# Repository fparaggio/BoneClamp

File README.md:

-------------------------------------------------------------------------

This file is part of the BoneClamp Data Conversion and Processing System
Copyright (C) 2013 BoneClamp

-------------------------------------------------------------------------

# BoneClamp
BoneClamp is an effort to create a fully programable, real-time, low-cost, data conversion and processing system for the 
[BeagleBone] (http://beagleboard.org/bone).

# More information
[BoneClamp Wiki] (https://potterlab.gatech.edu/main/newman/wiki/index.php?title=BoneClamp)

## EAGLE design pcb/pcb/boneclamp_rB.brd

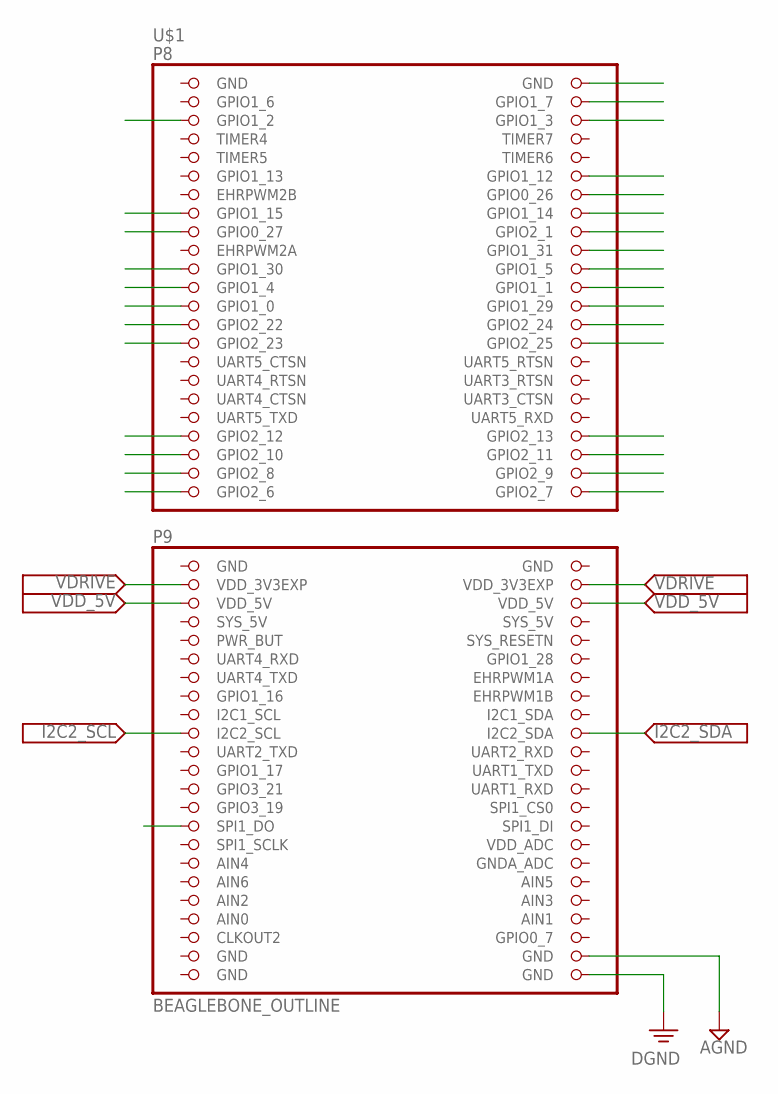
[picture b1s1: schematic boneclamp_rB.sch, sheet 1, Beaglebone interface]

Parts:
U$1: BEAGLEBONE_OUTLINE; BEAGLEBONE_SHIELD

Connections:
AGND: U$1.1 (GND), U$1.47 (GND), U$1.48 (GND), U$1.89 (GND), U$1.90 (GND), U$1.91 (GND); also elsewhere on the board
AIN0: U$1.85 (AIN0)
DGND: U$1.92 (GND); also elsewhere on the board
I2C2_SCL: U$1.65 (I2C2_SCL); also elsewhere on the board
I2C2_SDA: U$1.66 (I2C2_SDA); also elsewhere on the board
SYS_5V: U$1.53 (SYS_5V)
VDD_5V: U$1.51 (VDD_5V), U$1.52 (VDD_5V); also elsewhere on the board
VDRIVE: U$1.49 (VDD_3V3EXP), U$1.50 (VDD_3V3EXP); also elsewhere on the board

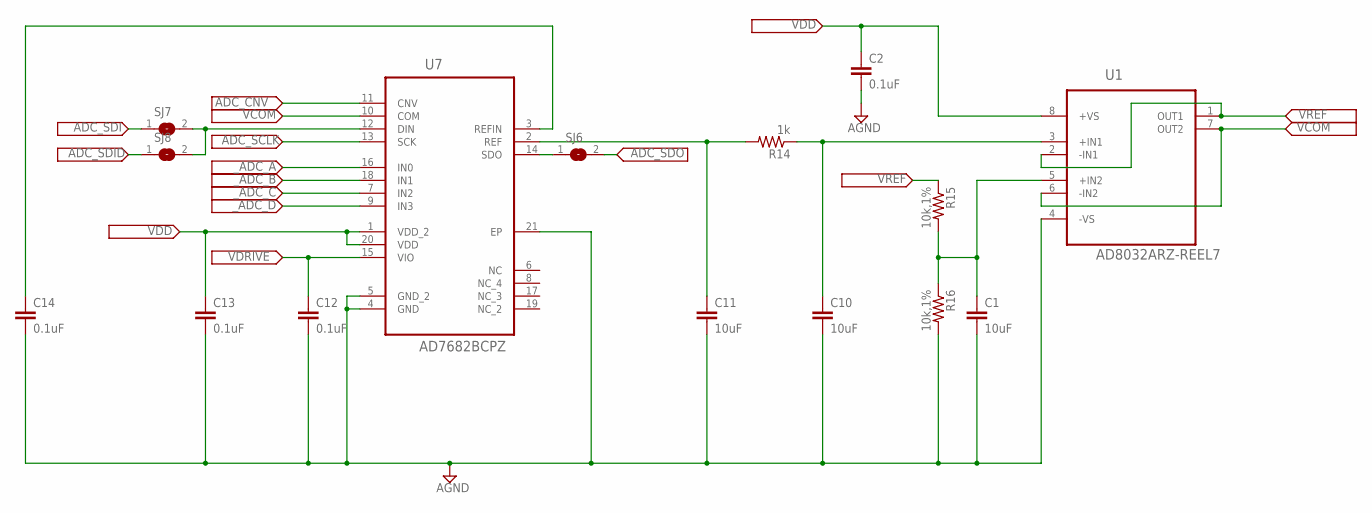
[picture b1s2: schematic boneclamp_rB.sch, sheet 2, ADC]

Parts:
C1, C10, C11: 10uF; C0805
C2, C12, C13, C14: 0.1uF; C0805
R14: 1k; R0805
R15, R16: 10k,1%; R0805
SJ6, SJ7, SJ8: SJ
U1: AD8032ARZ-REEL7; SOIC127P600X175-8N
U7: AD7682BCPZ; QFN50P400X400X100-21N

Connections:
ADC_CNV: U7.11 (CNV)
ADC_SCLK: U7.13 (SCK)
ADC_SDI: SJ7.1
ADC_SDID: SJ8.1
ADC_SDO: SJ6.2
AGND: C1.2, C2.2, C10.2, C11.2, C12.2, C13.2, C14.2, R16.2, U1.4 (-VS), U7.4 (GND), U7.5 (GND_2), U7.21 (EP); also elsewhere on the board
unnamed: C1.1, R15.2, R16.1, U1.5 (+IN2)
unnamed: SJ7.2, SJ8.2, U7.12 (DIN)
unnamed: C11.1, R14.2, U7.2 (REF)
unnamed: C10.1, R14.1, U1.3 (+IN1)
unnamed: C14.1, U7.3 (REFIN)
VCOM: U1.6 (-IN2), U1.7 (OUT2), U7.10 (COM)
VDD: C2.1, C13.1, U1.8 (+VS), U7.1 (VDD_2), U7.20 (VDD); also elsewhere on the board
VDRIVE: C12.1, U7.15 (VIO); also elsewhere on the board
VREF: R15.1, U1.1 (OUT1), U1.2 (-IN1); also elsewhere on the board
_ADC_A: U7.16 (IN0); also elsewhere on the board
_ADC_B: U7.18 (IN1); also elsewhere on the board
_ADC_C: U7.7 (IN2); also elsewhere on the board
_ADC_D: U7.9 (IN3); also elsewhere on the board

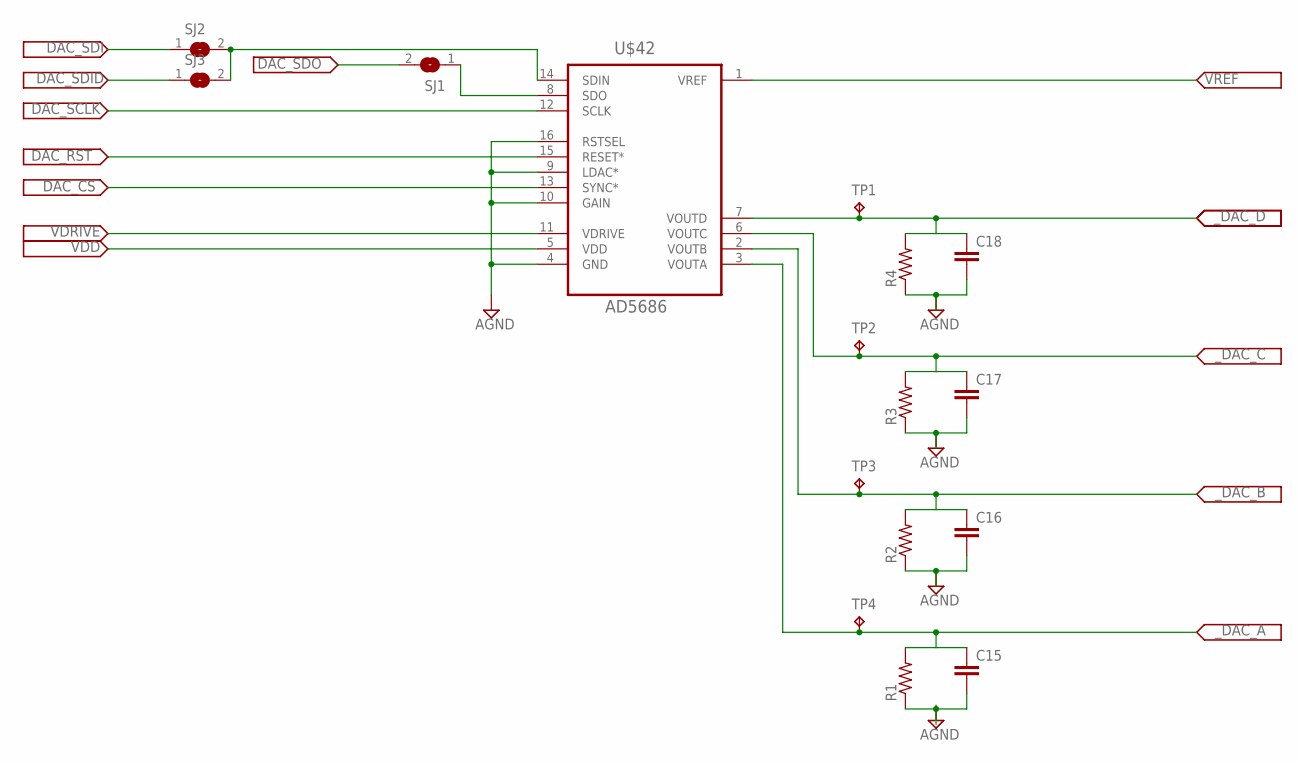
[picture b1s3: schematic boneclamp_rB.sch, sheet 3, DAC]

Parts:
C15, C16, C17, C18: C-EUC0805; C0805
R1, R2, R3, R4: R-US_R0805; R0805
SJ1, SJ2, SJ3: SJ
TP1, TP2, TP3, TP4: TPB1,27; B1,27
U$42: AD5686; MO-153-AB

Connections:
AGND: C16.2, C17.2, C18.2, R2.1, R3.1, R4.1, U$42.4 (GND), U$42.9 (LDAC*), U$42.10 (GAIN), U$42.16 (RSTSEL); also elsewhere on the board
DAC_CS: U$42.13 (SYNC*)
DAC_RST: U$42.15 (RESET*)
DAC_SCLK: U$42.12 (SCLK)
DAC_SDI: SJ2.1
DAC_SDID: SJ3.1
DAC_SDO: SJ1.2
unnamed: SJ1.1, U$42.8 (SDO)
unnamed: SJ2.2, SJ3.2, U$42.14 (SDIN)
unnamed: C15.2, R1.1
VDD: U$42.5 (VDD); also elsewhere on the board
VDRIVE: U$42.11 (VDRIVE); also elsewhere on the board
VREF: U$42.1 (VREF); also elsewhere on the board
_DAC_A: C15.1, R1.2, TP4.TP, U$42.3 (VOUTA); also elsewhere on the board
_DAC_B: C16.1, R2.2, TP3.TP, U$42.2 (VOUTB); also elsewhere on the board
_DAC_C: C17.1, R3.2, TP2.TP, U$42.6 (VOUTC); also elsewhere on the board
_DAC_D: C18.1, R4.2, TP1.TP, U$42.7 (VOUTD); also elsewhere on the board

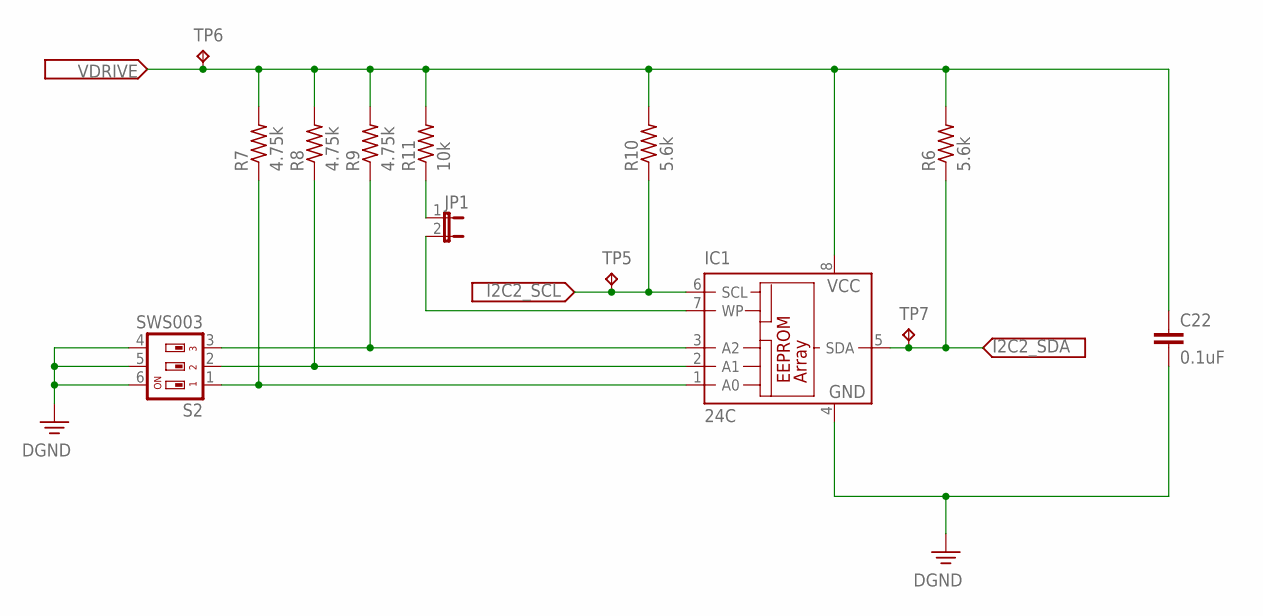
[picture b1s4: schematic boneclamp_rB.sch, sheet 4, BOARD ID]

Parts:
C22: 0.1uF; C0603
IC1: 24C; SO-08
JP1: JP1E; JP1
R6, R10: 5.6k; R0603
R7, R8, R9: 4.75k; R0603
R11: 10k; R0603
S2: SWS003; SMS-003
TP5, TP6, TP7: TPB1,27; B1,27

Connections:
DGND: C22.2, IC1.4 (GND), S2.4, S2.5, S2.6; also elsewhere on the board
I2C2_SCL: IC1.6 (SCL), R10.1, TP5.TP; also elsewhere on the board
I2C2_SDA: IC1.5 (SDA), R6.1, TP7.TP; also elsewhere on the board
unnamed: IC1.1 (A0), R7.1, S2.1
unnamed: IC1.2 (A1), R8.1, S2.2
unnamed: IC1.3 (A2), R9.1, S2.3
unnamed: IC1.7 (WP), JP1.2
unnamed: JP1.1, R11.1
VDRIVE: C22.1, IC1.8 (VCC), R6.2, R7.2, R8.2, R9.2, R10.2, R11.2, TP6.TP; also elsewhere on the board

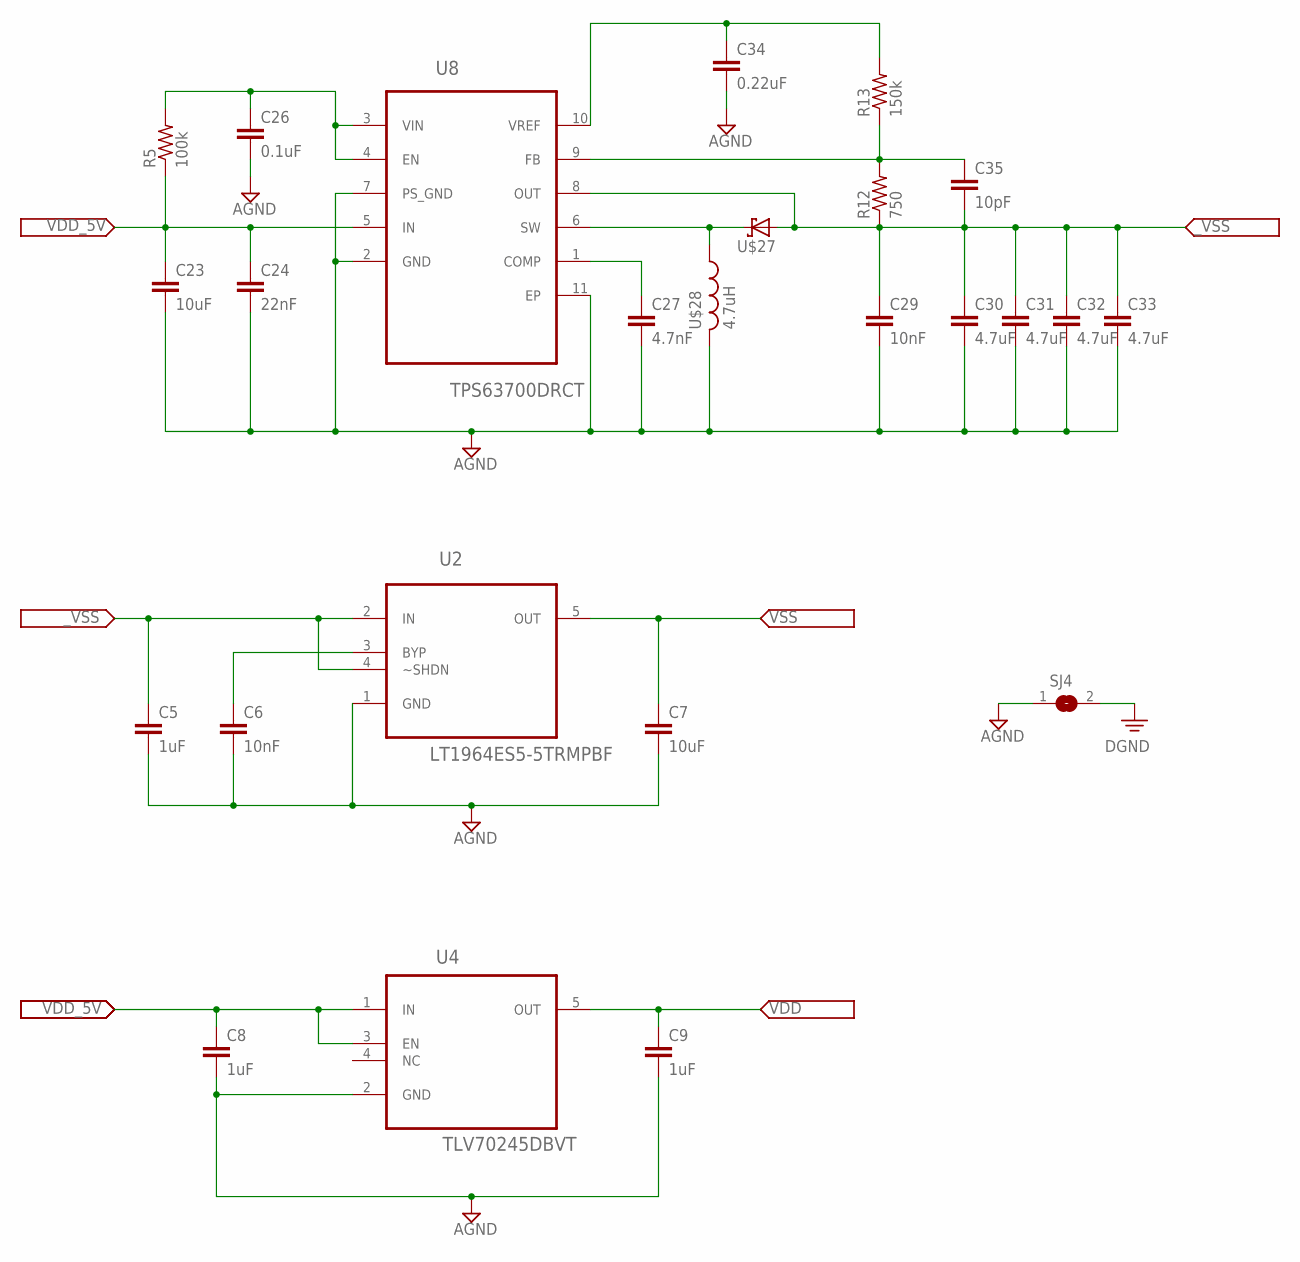
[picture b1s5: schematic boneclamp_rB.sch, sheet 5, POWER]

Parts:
C5, C8, C9: 1uF; C0805
C6, C29: 10nF; C0805
C7, C23: 10uF; C0805
C24: 22nF; C0805
C26: 0.1uF; C0805
C27: 4.7nF; C0805
C30, C31, C32, C33: 4.7uF; C0805
C34: 0.22uF; C0805
C35: 10pF; C0805
R5: 100k; R0805
R12: 750; R0805
R13: 150k; R0805
SJ4: SJ
U2: LT1964ES5-5TRMPBF; SOT95P280X100-5N
U4: TLV70245DBVT; SOT95P280X110-5N
U8: TPS63700DRCT; SON50P300X300X100-11N
U$27: SCHOTTKY-DIODE-2; DO-219AB
U$28: 4.7uH; L4012M

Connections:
AGND: C5.2, C6.2, C7.2, C8.2, C9.2, C23.2, C24.2, C26.2, C27.2, C29.2, C30.2, C31.2, C32.2, C33.2, C34.2, SJ4.1, U2.1 (GND), U4.2 (GND), U8.2 (GND), U8.7 (PS_GND), U8.11 (EP), U$28.2; also elsewhere on the board
DGND: SJ4.2; also elsewhere on the board
unnamed: C6.1, U2.3 (BYP)
unnamed: C26.1, R5.2, U8.3 (VIN), U8.4 (EN)
unnamed: C27.1, U8.1 (COMP)
unnamed: U8.6 (SW), U$27.P$1 (A), U$28.1
unnamed: C35.1, R12.2, R13.1, U8.9 (FB)
unnamed: C34.1, R13.2, U8.10 (VREF)
VDD: C9.1, U4.5 (OUT); also elsewhere on the board
VDD_5V: C8.1, C23.1, C24.1, R5.1, U4.1 (IN), U4.3 (EN), U8.5 (IN); also elsewhere on the board
VSS: C7.1, U2.5 (OUT); also elsewhere on the board
_VSS: C5.1, C29.1, C30.1, C31.1, C32.1, C33.1, C35.2, R12.1, U2.2 (IN), U2.4 (~SHDN), U8.8 (OUT), U$27.P$2 (C)

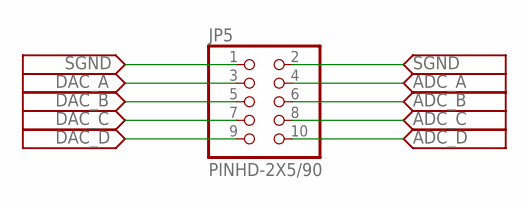
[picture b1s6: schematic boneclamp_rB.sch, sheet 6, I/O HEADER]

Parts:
JP5: PINHD-2X5/90; 2X05/90

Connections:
ADC_A: JP5.4; also elsewhere on the board
ADC_B: JP5.6; also elsewhere on the board
ADC_C: JP5.8; also elsewhere on the board
ADC_D: JP5.10; also elsewhere on the board
DAC_A: JP5.3
DAC_B: JP5.5
DAC_C: JP5.7
DAC_D: JP5.9
SGND: JP5.1, JP5.2

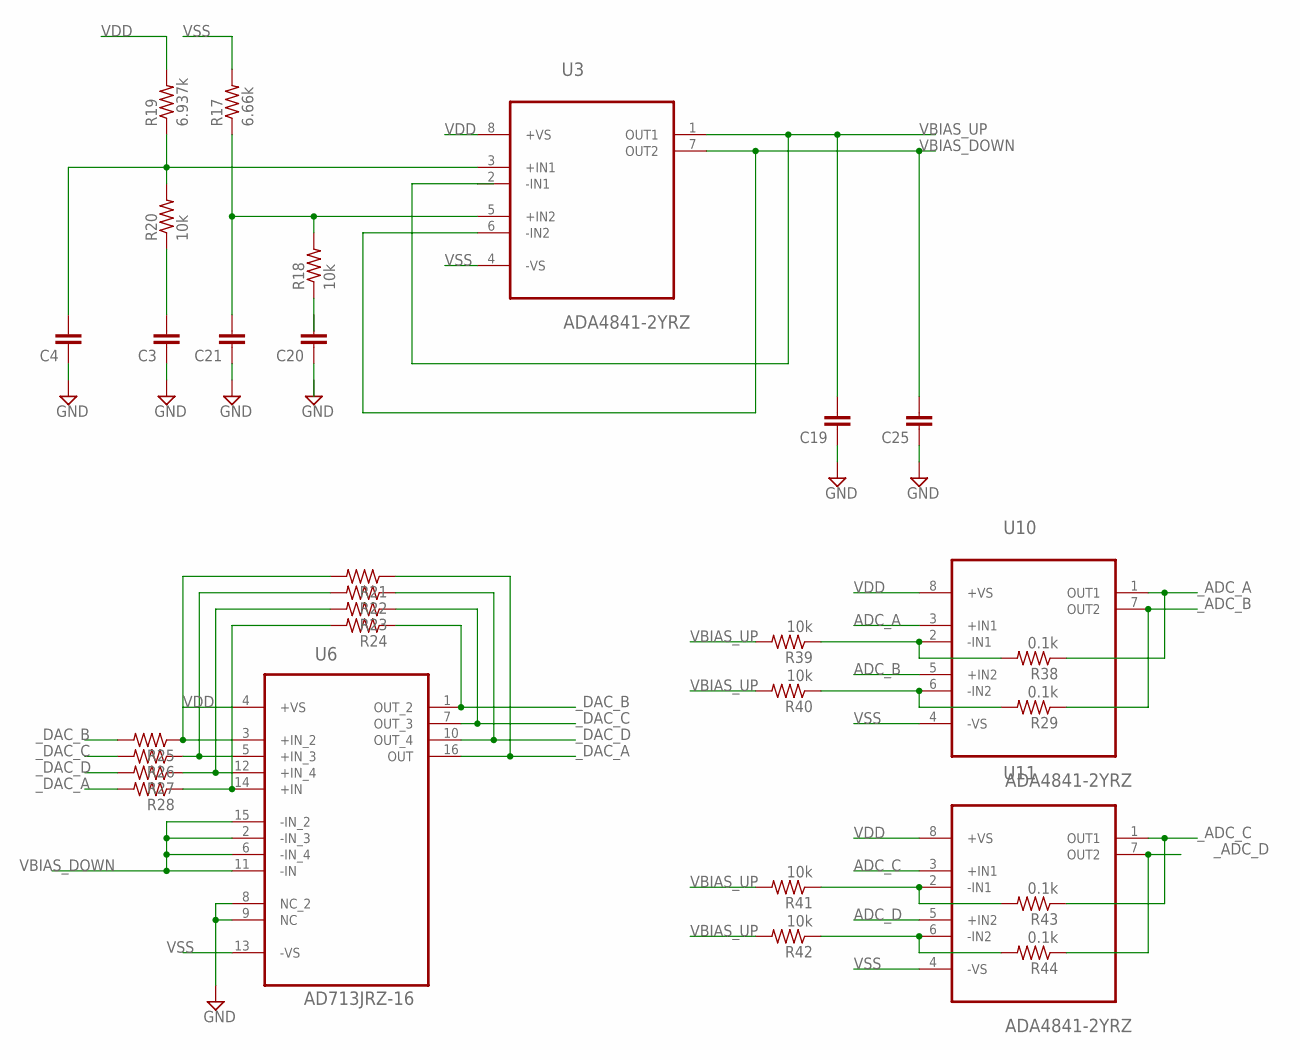
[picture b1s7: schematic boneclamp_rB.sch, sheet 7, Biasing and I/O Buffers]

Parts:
C3, C4, C19, C20, C21, C25: C-EU025-025X050; C025-025X050
R17: 6.66k; 0204V
R18, R20: 10k; 0204V
R19: 6.937k; 0204V
R21, R22, R23, R24, R25, R26, R27, R28: R-US_0204/2V; 0204V
R29, R38, R43, R44: 0.1k; R0805
R39, R40, R41, R42: 10k; R0805
U3, U10, U11: ADA4841-2YRZ; SOIC127P600X175-8N
U6: AD713JRZ-16; SOIC127P1032X265-16N

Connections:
ADC_A: U10.3 (+IN1); also elsewhere on the board
ADC_B: U10.5 (+IN2); also elsewhere on the board
ADC_C: U11.3 (+IN1); also elsewhere on the board
ADC_D: U11.5 (+IN2); also elsewhere on the board
GND: C3.1, C4.1, C19.1, C21.1, C25.1, U6.8 (NC_2), U6.9 (NC)
unnamed: R24.2, R28.1, U6.14 (+IN)
unnamed: R23.2, R27.1, U6.12 (+IN_4)
unnamed: C21.2, R17.1, R18.2, U3.5 (+IN2)
unnamed: C4.2, R19.1, R20.2, U3.3 (+IN1)
unnamed: R22.2, R26.1, U6.5 (+IN_3)
unnamed: R21.2, R25.1, U6.3 (+IN_2)
unnamed: C3.2, R20.1
VBIAS_DOWN: C25.2, U3.6 (-IN2), U3.7 (OUT2), U6.2 (-IN_3), U6.6 (-IN_4), U6.11 (-IN), U6.15 (-IN_2)
VBIAS_UP: C19.2, R29.2, R38.2, R39.1, R39.2, R40.1, R40.2, R41.1, R41.2, R42.1, R42.2, R43.2, R44.2, U3.1 (OUT1), U3.2 (-IN1), U10.2 (-IN1), U10.6 (-IN2), U11.2 (-IN1), U11.6 (-IN2)
VDD: R19.2, U3.8 (+VS), U6.4 (+VS), U10.8 (+VS), U11.8 (+VS); also elsewhere on the board
VSS: R17.2, U3.4 (-VS), U6.13 (-VS), U10.4 (-VS), U11.4 (-VS); also elsewhere on the board
_ADC_A: R38.1, U10.1 (OUT1); also elsewhere on the board
_ADC_B: R29.1, U10.7 (OUT2); also elsewhere on the board
_ADC_C: R43.1, U11.1 (OUT1); also elsewhere on the board
_ADC_D: R44.1, U11.7 (OUT2); also elsewhere on the board
_DAC_A: R21.1, R28.2, U6.16 (OUT); also elsewhere on the board
_DAC_B: R24.1, R25.2, U6.1 (OUT_2); also elsewhere on the board
_DAC_C: R23.1, R26.2, U6.7 (OUT_3); also elsewhere on the board
_DAC_D: R22.1, R27.2, U6.10 (OUT_4); also elsewhere on the board

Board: 4 copper layers, 101 parts (0 on the bottom side), 53 nets, no tracks yet.

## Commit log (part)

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2013-01-31 Added a prototyping folder containing the intial list of proto supplies.
2013-01-31 Added folder to contain PCB design files. We will use EAGLE for PCB creation.
2013-02-01 Made some modifications to the proto parts list
2013-02-01 adding training materials
2013-02-10 - added img folder to contain useful images from our collective writtings about the BC
2013-02-14 Added a pru folder. This has the am355x diy package that Jon has on his repo. After being unable to figure out how to read from pru memory pools, I added a read function to the prussdrv.c device driv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
2013-02-14 Getting to grips with git, everything should be up now
2013-02-14 Cleaning up after Kristaps
2013-02-14 Adding PRU stuff
2013-02-15 Added eagle libraries that contain the Analog Devices ICs that we will be using (both AD7656YSTZ and AD5754BREZ)
2013-02-16 Cleanup
2013-02-16 Added parts libraries for audio jack connector and the BB cape layout
2013-02-16 Added extended TI device library
2013-02-16 Added data-sheets for ICs on the board. Also, I started an EAGLE schematic that contains the parts we know will be on the board: the expansion headers along with their correct layout, the ADC, the DA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
2013-02-18 Added data sheet for the TRS jack
2013-02-20 Update .gitignore
    Spelling mistakes.
2013-02-24 Updated the adafruit libary to include the d-sub connector we will be using. Updated .gitignore to ingore libary backups. Started a power supply sheet on the eagle schematic.
2013-02-24 Added 15 pin HD DSUB connector data sheet
2013-02-24 Renamed the pcb folder to be more in line with other directory names
2013-02-24 Started working through the basic wiring on the schematic, connectrating on grounds, power, and analog IO
2013-02-25 Added optional compensation comoponents and test points to DAC output lines. Added a right angle 0.1 inch pitch header for outside power input.
2013-02-25 Added pictures of the effective jitter, as seen on an oscope, while running the pw_gpio_sin example
2013-02-27 I put an anti-aliasing filter design tool, provided by TI, into the PCB folder. The stop frequency (the frequency at which the attenuation is equal to the noise floor of the ADC (NOT the -3 dB point)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
2013-02-28 Adding non-rt port of rtxi for front end user - in progress
2013-03-03 Found a good regulator for powering the BB using the +/- 6 to 12 volt rails required to use the boneclamp. Updated schematic and added data sheet to data-sheets folder
2013-03-03 Started and examples folder containing information about good capes produced by other people
2013-03-03 Renamed file
2013-03-03 Added data sheet for DIPswitch
2013-03-03 Added external 2.5 volt references for DAC and ADC. This circuit needs a buffer option which can be feed into the 3 position jumper.
2013-03-07 added directory structure (in pru/boneclamp/) for actual project
2013-03-07 Removed some stray backups that were just cluttering things up
2013-03-07 Adding buildrood directory
2013-03-07 updating front-end user interface requirements
2013-03-09 Added new data sheets. Started a second pcb layout for new DAC/ADC unipolar solutions.
2013-03-09 Moved the proto list directory to its proper location
2013-03-09 More changes to circuit
2013-03-09 Renamed the old boneclamp schematic and board
2013-03-09 Orgnanized data sheets
2013-03-09 Worked a bit on the schematic
2013-03-10 Adding OS files
2013-03-10 Wired the DC-DC inverter
2013-03-10 Added negative LDO regulator
2013-03-10 Added data sheet for +5V LDO reg.
2013-03-10 Minor schematic edit
2013-03-10 Updated BOM
2013-03-11 Added data sheets for the smd-to-dip adapters we will use. Minor changes to schematic
2013-03-12 Moved BOMs to their own directory
2013-03-12 Finished power supply circuits on schematic. Updated BOM and added new data sheets.
2013-03-13 Updated adafruit library with 2X5 0.1 inch pitch header, which we will use for I/O on the BC. Added that to the schematic
2013-03-13 Finished basic ADC module
2013-03-14 Added buffered VREF divider, which feeds back into ADC to get bipolar input swing.
2013-03-14 Removed obsolete design-notes file
2013-03-14 Finished digital input to DAC
2013-03-14 This can now actually be built (tested only on x86_64 using arm-none-linux-gnueabi-gcc). Makefile now automatically decides if cross compilation necessary (to avoid typing ' CROSS_COMPILE = ' every t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
2013-03-15 Commits
2013-03-15 Minor fixed to EEPROM circuit and ADC VREF buffer. Stephano, don't kill me.
2013-03-15 Added evaluation board PDFs to the data-sheets folder
2013-03-15 updating config files to detect sys envs
2013-03-17 Added another example cape, this one has the exact dimensions we are interested in and is well documented.
2013-03-17 Minor edit
2013-03-18 Updating BoneClampOS configs
2013-03-18 non-RT interface for boneclamp
2013-03-18 Finishing up xi-bone UI
2013-03-18 Almost done with UI - need to write up quick install script
2013-03-18 updating license
2013-03-18 Updating readme and license
2013-03-18 xi-bone 94.62% complete
2013-03-18 Fixed the BB Daughter board layout to include power management header (p6) and extended board area
2013-03-19 Added Ground and power plane to pcb. Power plane will need to be split into primarly VDD and then a bit at the front of the board for VSS. VDD and VSS planes should not overlap in the Z direction.
2013-03-19 Updating licensing information
2013-03-19 Cleaning up files
2013-03-19 Licensing done
2013-03-19 Adding author information
2013-03-19 Properly bypassed the power and logic supplies for the DAC
2013-03-20 Hi, Jon
2013-03-20 Direct write from PRU shared mem to user space ddr
2013-03-21 Added voltage biasing
2013-03-22 Adding server/client communication
2013-03-22 PRU mods and now testing DAC from Jon
2013-03-22 removing old netcomm files
2013-03-23 Added Stefano's biasing circuitry back into the master branch schematic. Automatic merge was not going to work properly
2013-03-23 Added DC-DC boost option. Reoganized data sheets
2013-03-23 Added pinout info for the bus pirate. Created a logic-sniffer project to examine the SPI signals sent to the chips. DAC is working nicely.
2013-03-24 I found a potentially better option for the ADC. It is a 100KSPS Serial sampling device from TI. It accepts true bipolar signals of +-VREF using a single supply. It also has as a more resonable SMD p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
2013-03-24 Added information on the lm2663 DC-DC switch capacitor voltage inverter. A much better option than the inductor based inverter we are currently using.
2013-03-25 Added yet another option to explore for the ADC. I need to make some calls to find out what the best option is. There is always something wrong with any particular choice.
2013-03-25 Added data sheet for the ADS88331, which is probably the best converter option so far.
2013-03-26 Added the 8331 to schematic. I'm pretty sure this is the right ADC.
2013-03-27 Added excellent choice for external 2.048 VREF. This data sheet includes the circuit for creating a bipolar reference.
2013-03-27 ADC-SPI 95%
2013-03-29 Too optimistic - PRU still needs some work but mostly there
2013-03-29 Minor fixes to voltage bias followers
2013-03-31 Added data sheet for MCP8024 in the proto folder. This ADC will be helpful for troubleshooting the SPI interface since it is low cost and easy to play with.
2013-04-01 Finished basics of input stage to new 8331 and some of the digital interface for it.
2013-04-01 Added the switched capacitor voltage inveter, which greatly simiplifies the power supply design.
2013-04-04 Ring buffer for PRU to userspace comms. Still under construction
2013-04-04 Fixed DAC output bias
    Biased DAC output, other minor schematic changes
2013-04-06 Tagged v0.1 as the last version to contain an effort to implement daisy chaining. This can serve as point of reference if we want to revisit that in the future.
2013-04-06 Cleaned up schematic to get it ready for actual component selection (passive commoponent packages) and final wiring.
2013-04-06 Updating host app
2013-04-06 adding hdf tools
2013-04-06 Added data sheet for the MAX1735, which is a good choice for our negative rail. I calculated the basic power requirements for the chips we are using and this should be good except with the DAC outs a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
2013-04-06 Replaced negative LDO with the MAX1735.
2013-04-07 Uninverted DAC output bias, found alternative amp
2013-04-07 Simplest I/O biasing scheme yet.
2013-04-07 Nearly finished with full circuit.I need the GPIO pins that we will be using.
2013-04-07 Started double checking bypassing on each IC.
2013-04-08 Minor schematic changes.
2013-04-18 getting rid of crap files
2013-04-18 Rewriting ring buffer to use pointers instead of indices. Currently it is a mess and cannot be built. Will resume work later today or tomorrow
2013-04-18 Repackaged passive components.
    Shrank all passive components, verified their viability.
2013-04-18 Removed annoying stray curly brace in something.c
2013-04-18 Started implmenenting Amanda's comments.
2013-04-19 Took care of most of Amanda's comments. Started using data buses instead of individual nets for the SPI interfaces.
2013-04-20 Started renaming test points, etc.
2013-04-20 More reorganization.
2013-04-20 Started getting rid of signal tag symbols, take too much room and cause problems with automatic component renumbering.
2013-04-20 Renumbered all components.
2013-04-20 Schematic nearly done. Checking/updating BOM.
2013-04-20 Finished BOM.
2013-04-20 Minor fix.
2013-04-20 Started layout.
2013-04-21 Routed VDRIVE out from bbehind switching supply using power plane. Following regulation +/-4.5v will dive into power plane and occupy it with VDRIVE. SPI signals should originate from p8 if at all po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
2013-04-21 Added split GND plane.
2013-04-21 Started EEPROM circuit.
2013-04-22 Testing DMA memory access, pru0 combo, and a few other tricks
2013-04-23 Rewritting ring buffer to use pointers instead of indices. Oddly, having trouble loading assembly code to the PRU (fopen() inside prussdrv_exec_program() segfaults)
2013-04-26 Committed breakout board
2013-05-02 Started laying out the AO buffer stage.
2013-05-02 Finished basic DAC buffer layout.
2013-05-02 Minore changes.
2013-05-03 Finalizing DAC/ADC buffer layout.
2013-05-03 Analog buffering stage is pretty much finished. Next will be the regulated power circuitry, then comes the mixed signal ICs.
2013-05-03 Halfway through analog filters.
2013-05-03 Routed v regulation.
2013-05-04 Fixed the ground planes.
2013-05-04 Routed the SPI buses.
2013-05-06 DAC bypassing complete.
2013-05-09 Started to route IC groups together.
2013-05-10 Routing.
2013-05-10 More routing.
2013-05-10 Routing almost complete.
2013-05-10 Updating ads8331 spi
2013-05-10 Labelled GPIO pins that we will use for SPI busses.
2013-05-11 GPIO implemented; Think it's right, need to test tonightish
2013-05-11 adding simple ring buffer with atomic calls; should do the trick for us
2013-05-11 Updating Buffer
2013-05-11 updating makefile
2013-05-11 Starting network comm protocol work
2013-05-11 Update .gitignore
    Updated to ignore mach-dep compiled shared objects.
2013-05-11 Finished first intetation of routing! Need to clean up the silkscreen, check for single ended wires, double check schematic wiring, run DRC, and send it to fab.
2013-05-11 Nearly done with silkscreen.
2013-05-12 Fixed some random problems with the silkscreen.
2013-05-12 More minor silkscreen issues. Started drawing logo.
2013-05-12 Updating PRU
2013-05-12 modifying gpio control
2013-05-12 updating labels for DAC SPI
2013-05-12 Adding ADC GPIO directions
2013-05-12 Adding 4th DAC SPI pin on GPIO1_13
2013-05-12 Updating DAC SPI GPIO pin directions
2013-05-12 Updating PRU.c
2013-05-12 Re-added the DAC SDO line.
2013-05-12 Got rid of autogen eagle file.
2013-05-12 Added logo to board.
2013-05-12 Minor silkscreen stuff.
2013-05-12 Updating PRU files; memory initialization error in PRU exec program
2013-05-12 Created CAM job to work with OSH Park.
2013-05-12 Reorganizing.
2013-05-12 Got rid of the breakout board.
2013-05-12 Renamed the board.
2013-05-12 Finished the silkscreen stuff.
2013-05-12 Updated ignore rules.
